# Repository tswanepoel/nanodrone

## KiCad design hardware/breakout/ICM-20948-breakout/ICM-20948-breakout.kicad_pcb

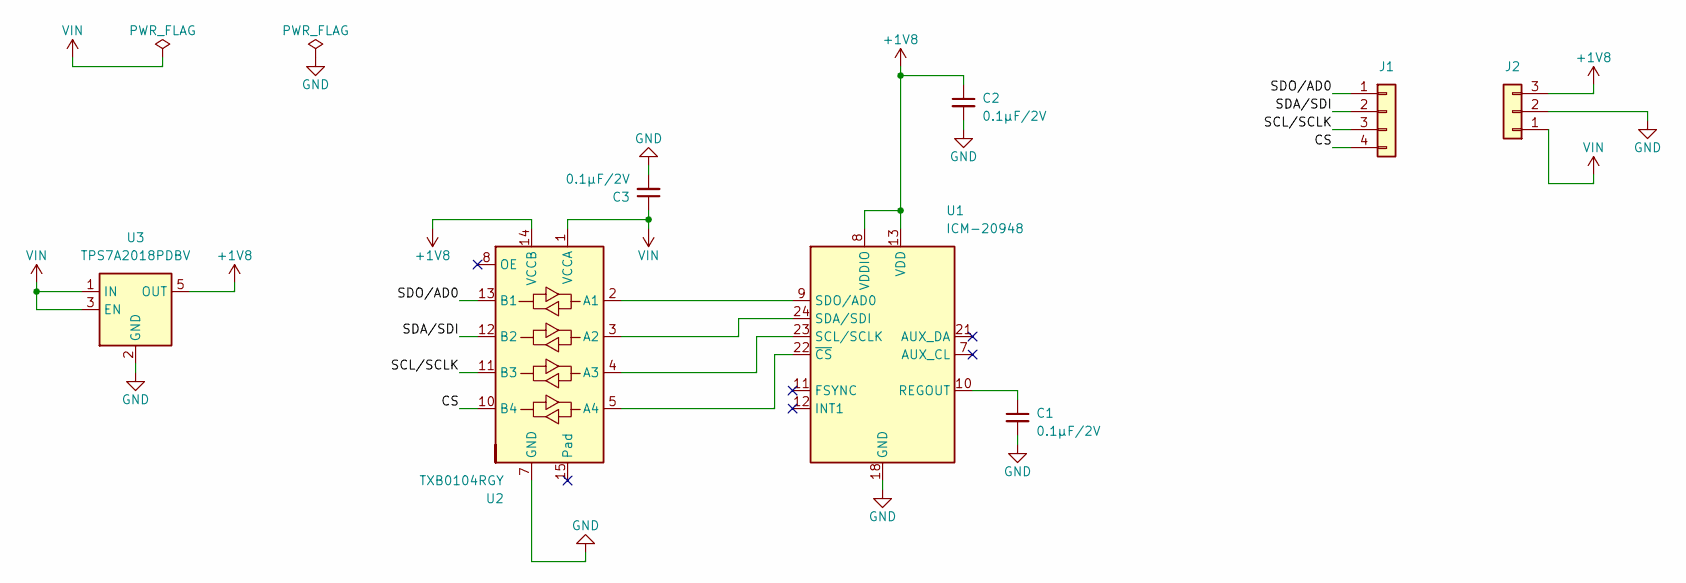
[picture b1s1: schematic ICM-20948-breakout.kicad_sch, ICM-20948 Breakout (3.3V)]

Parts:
C1, C2, C3: 0.1µF/2V; C_0603_1608Metric_Pad1.08x0.95mm_HandSolder
J1: Conn_01x04; PinHeader_1x04_P2.54mm_Vertical
J2: Conn_01x03; PinHeader_1x03_P2.54mm_Vertical
U1: ICM-20948; InvenSense_QFN-24_3x3mm_P0.4mm
U2: TXB0104RGY; Texas_S-PVQFN-N14
U3: TPS7A2018PDBV; SOT-23-5

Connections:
+1V8: C2.1, J2.3, U1.8 (VDDIO), U1.13 (VDD), U2.14 (VCCB), U3.5 (OUT)
/CS: J1.4, U2.10 (B4)
/SCL/SCLK: J1.3, U2.11 (B3)
/SDA/SDI: J1.2, U2.12 (B2)
/SDO/AD0: J1.1, U2.13 (B1)
GND: C1.2, C2.2, C3.2, J2.2, U1.18 (GND), U1.20 (GND), U2.7 (GND), U3.2 (GND)
unnamed: C1.1, U1.10 (REGOUT)
unnamed: U1.23 (SCL/SCLK), U2.4 (A3)
unnamed: U1.24 (SDA/SDI), U2.3 (A2)
unnamed: U1.9 (SDO/AD0), U2.2 (A1)
unnamed: U1.22 (~CS), U2.5 (A4)
VIN: C3.1, J2.1, U2.1 (VCCA), U3.1 (IN), U3.3 (EN)

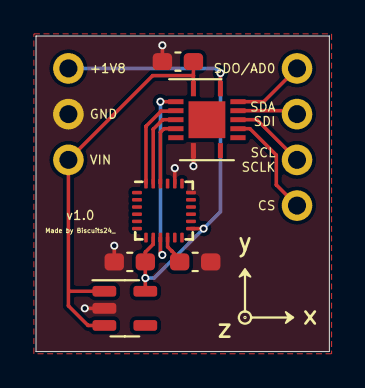
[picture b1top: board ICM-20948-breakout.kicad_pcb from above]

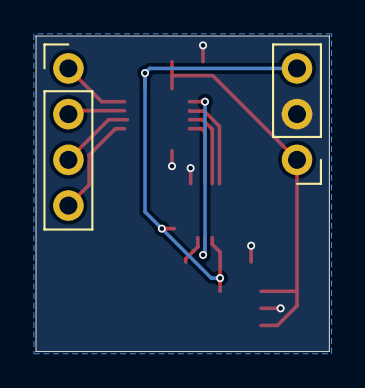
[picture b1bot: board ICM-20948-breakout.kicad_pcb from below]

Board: 2 copper layers, 16.3 x 17.5 mm, 8 parts (2 on the bottom side), 12 nets.

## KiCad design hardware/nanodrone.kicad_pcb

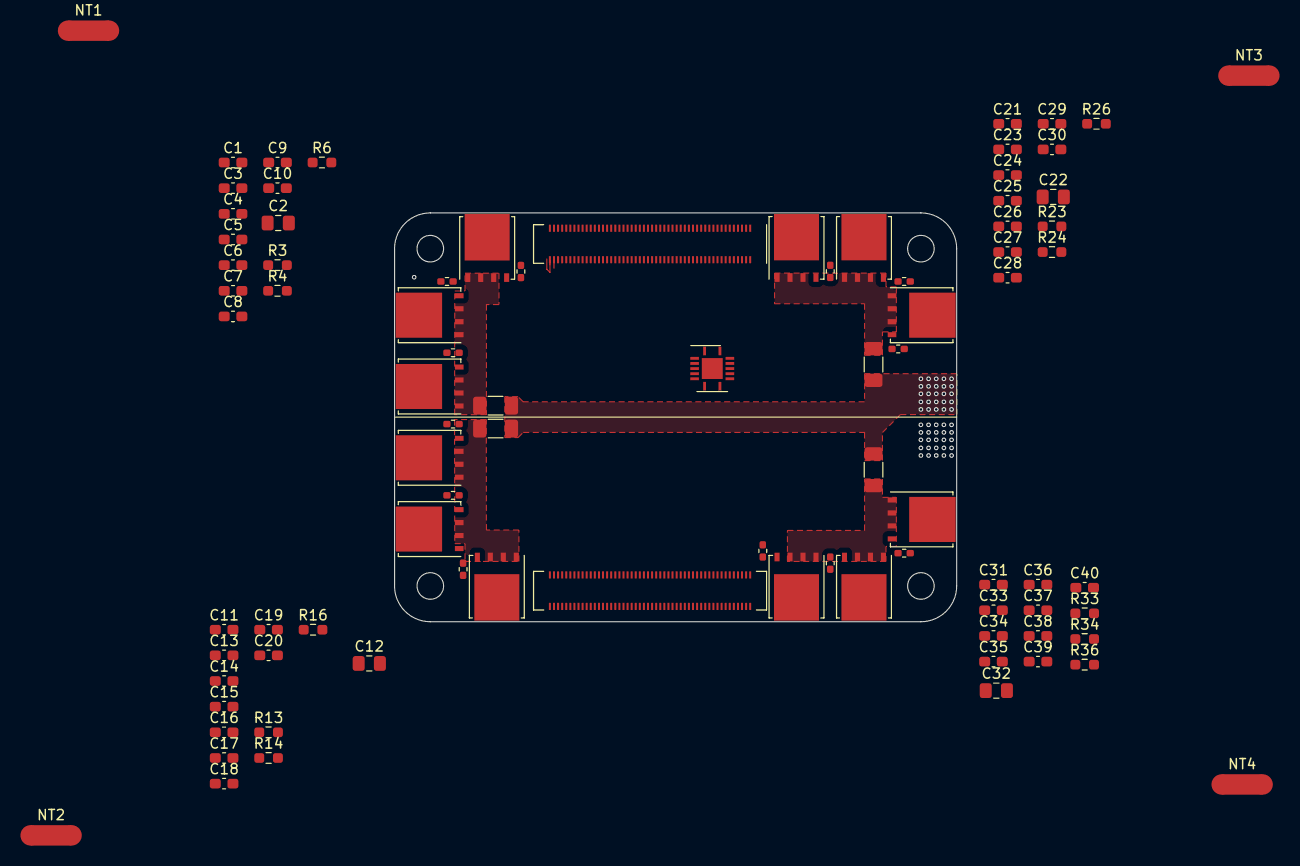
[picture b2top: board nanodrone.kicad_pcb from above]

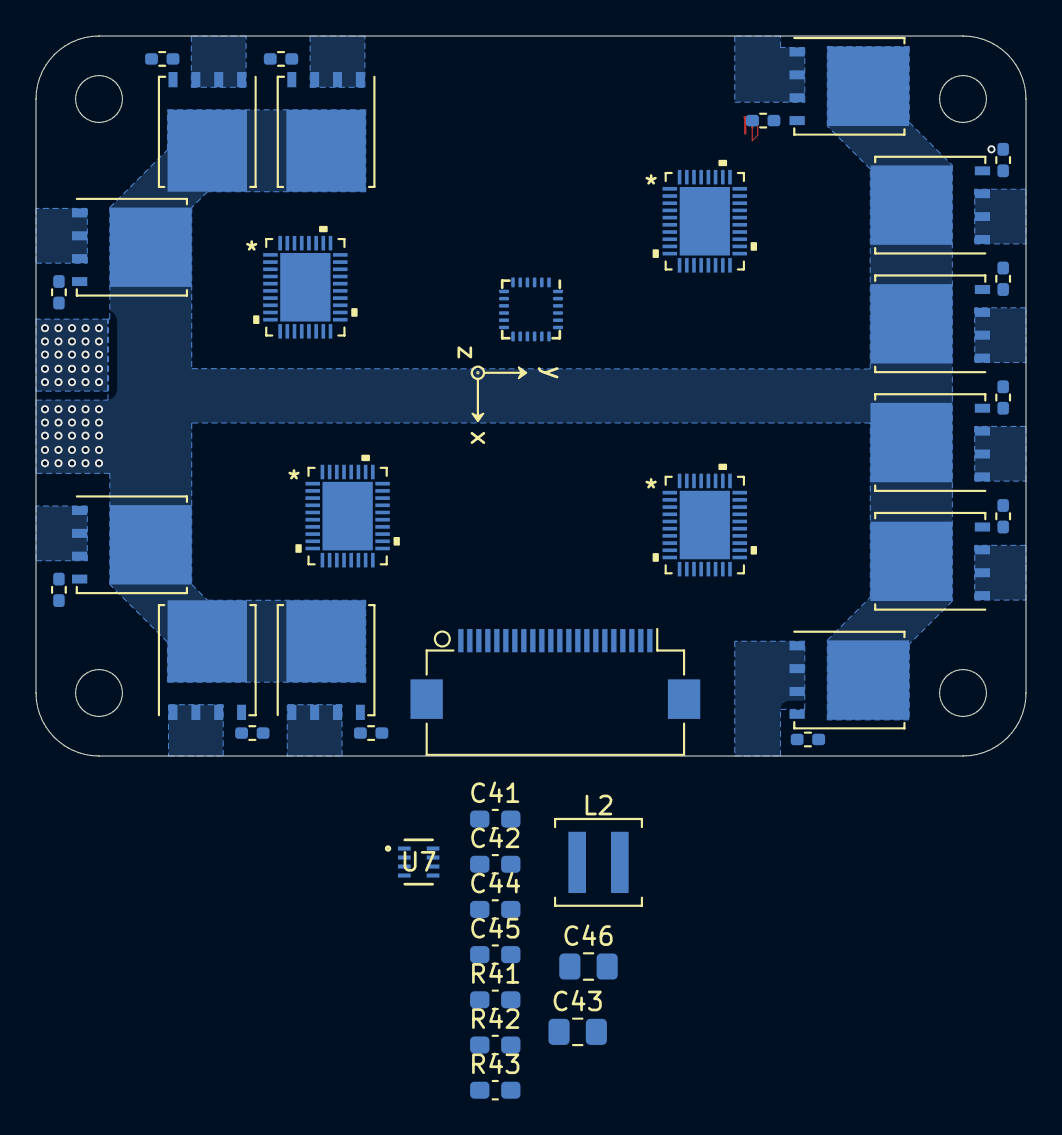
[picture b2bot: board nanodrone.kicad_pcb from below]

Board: 4 copper layers, 55.0 x 40.0 mm, 127 parts (41 on the bottom side), 126 nets.

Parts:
C1, C11, C21, C31: 0.1µF/25V; C_0603_1608Metric_Pad1.08x0.95mm_HandSolder
C2, C12, C22, C32: 10µF/25V; C_0805_2012Metric_Pad1.18x1.45mm_HandSolder
C3, C13, C23, C33: 470nF/25V; C_0603_1608Metric_Pad1.08x0.95mm_HandSolder
C4, C14, C24, C34: 10µF/25V; C_0603_1608Metric_Pad1.08x0.95mm_HandSolder
C5, C15, C25, C35: 1µF/10V; C_0603_1608Metric_Pad1.08x0.95mm_HandSolder
C6, C8, C9, C16, C18, C19, C26, C28, C29, C36, C38, C39: 1µF/25V; C_0603_1608Metric_Pad1.08x0.95mm_HandSolder
C7, C17, C27, C37: 1µF/4V; C_0603_1608Metric_Pad1.08x0.95mm_HandSolder
C10, C20, C30, C40: 1µF/6.3V; C_0603_1608Metric_Pad1.08x0.95mm_HandSolder
C41: 100nF/10V; C_0603_1608Metric_Pad1.08x0.95mm_HandSolder
C42: 100nF/25V; C_0603_1608Metric_Pad1.08x0.95mm_HandSolder
C43: 10µF/35V; C_0805_2012Metric_Pad1.18x1.45mm_HandSolder
C44: 33nF/10V; C_0603_1608Metric_Pad1.08x0.95mm_HandSolder
C45: 47pF/25V; C_0603_1608Metric_Pad1.08x0.95mm_HandSolder
C46: 47µF/10V; C_0805_2012Metric_Pad1.18x1.45mm_HandSolder
J1: Conn_01x22_Female; Hirose_FH12A-22S-0.5SH_1x22-1MP_P0.50mm_Horizontal
L2: 3.3µH; L_Coilcraft_XAL4030-XXX
Module1: ComputeModule4-CM4; Raspberry-Pi-4-Compute-Module
NT1, NT2, NT3, NT4: NetTie_2; NetTie-2_SMD_Pad2.0mm
Q1, Q2, Q3, Q4, Q5, Q6, Q7, Q8, Q9, Q10, Q11, Q12, Q13, Q14, Q15, Q16, Q17, Q18, Q19, Q20, Q21, Q22, Q23, Q24: BSC009NE2LS5; TDSON-8-1
R1, R2, R5, R7, R8, R9, R11, R12, R15, R17, R18, R19, R21, R22, R25, R27, R28, R29, R31, R32, R35, R37, R38, R39: 0Ω; R_0402_1005Metric_Pad0.72x0.64mm_HandSolder
R3, R4, R13, R14, R23, R24, R33, R34: 10kΩ; R_0603_1608Metric_Pad0.98x0.95mm_HandSolder
R6, R16, R26, R36: 5.1kΩ; R_0603_1608Metric_Pad0.98x0.95mm_HandSolder
R10, R20, R30, R40: 1mΩ/1W; R_1206_3216Metric_Pad1.30x1.75mm_HandSolder
R41: 19.6kΩ; C_0603_1608Metric_Pad1.08x0.95mm_HandSolder
R42: 52.3kΩ; C_0603_1608Metric_Pad1.08x0.95mm_HandSolder
R43: 10kΩ; C_0603_1608Metric_Pad1.08x0.95mm_HandSolder
U1, U2, U5, U6: MCT8329A; MCT8329A1IREER
U3: TXB0104RGY; Texas_S-PVQFN-N14
U4: ICM-20948; InvenSense_QFN-24_3x3mm_P0.4mm
U7: TPS62933FDRLR; SOT_33DRLR_TEX

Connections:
/CAM1_C_N: J1.8, Module1.127 (CAM1_C_N)
/CAM1_C_P: J1.9, Module1.129 (CAM1_C_P)
/CAM1_D0_N: J1.2, Module1.115 (CAM1_D0_N)
/CAM1_D0_P: J1.3, Module1.117 (CAM1_D0_P)
/CAM1_D1_N: J1.5, Module1.121 (CAM1_D1_N)
/CAM1_D1_P: J1.6, Module1.123 (CAM1_D1_P)
/CAM1_D2_N: J1.11, Module1.133 (CAM1_D2_N)
/CAM1_D2_P: J1.12, Module1.135 (CAM1_D2_P)
/CAM1_D3_N: J1.14, Module1.139 (CAM1_D3_N)
/CAM1_D3_P: J1.15, Module1.141 (CAM1_D3_P)
/SCL0: J1.20, Module1.80 (SCL0)
/SDA0: J1.21, Module1.82 (SDA0)
AGND: C30.2, C40.2, U5.25 (AGND), U6.25 (AGND)
AVDD: C5.1, C10.1, C15.1, C20.1, C25.1, C30.1, C35.1, C40.1, R6.1, R16.1, R26.1, R36.1, U1.2 (VREG), U1.26 (AVDD), U2.2 (VREG), U2.26 (AVDD), U5.2 (VREG), U5.26 (AVDD), U6.2 (VREG), U6.26 (AVDD)
DGND: U1.1 (DGND), U2.1 (DGND), U5.1 (DGND), U6.1 (DGND)
DVDD: C7.1, C17.1, C27.1, C37.1, U1.36 (DVDD), U2.36 (DVDD), U5.36 (DVDD), U6.36 (DVDD)
GND: C4.2, C10.2, C14.2, C20.2, C24.2, C34.2, J1.1, J1.4, J1.7, J1.10, J1.13, J1.16, J1.19, Module1.113 (GND), Module1.119 (GND), Module1.125 (GND), Module1.131 (GND), Module1.137 (GND), NT1.2, NT2.2, NT3.2, NT4.2, R3.2, R4.1, R13.2, R14.1, R23.2, R24.1, R33.2, R34.1, U1.25 (AGND), U2.25 (AGND)
unnamed: C45.1, C46.1, L2.2, R42.1
unnamed: Q1.4 (G), R1.1
unnamed: C6.2, Q1.1 (S), Q1.2 (S), Q1.3 (S), Q2.5 (D), U1.10 (SHA)
unnamed: Q2.4 (G), R2.1
unnamed: Q3.4 (G), R5.1
unnamed: C8.2, Q3.1 (S), Q3.2 (S), Q3.3 (S), Q4.5 (D), U1.14 (SHB)
unnamed: Q4.4 (G), R7.1
unnamed: Q5.4 (G), R8.1
unnamed: C9.2, Q5.1 (S), Q5.2 (S), Q5.3 (S), Q6.5 (D), U1.18 (SHC)
unnamed: Q6.4 (G), R9.1
unnamed: Q7.4 (G), R11.1
unnamed: C16.2, Q7.1 (S), Q7.2 (S), Q7.3 (S), Q8.5 (D), U2.10 (SHA)
unnamed: Q8.4 (G), R12.1
unnamed: Q9.4 (G), R15.1
unnamed: C18.2, Q9.1 (S), Q9.2 (S), Q9.3 (S), Q10.5 (D), U2.14 (SHB)
unnamed: Q10.4 (G), R17.1
unnamed: Q11.4 (G), R18.1
unnamed: C19.2, Q11.1 (S), Q11.2 (S), Q11.3 (S), Q12.5 (D), U2.18 (SHC)
unnamed: Q12.4 (G), R19.1
unnamed: Q13.4 (G), R21.1
unnamed: C26.2, Q13.1 (S), Q13.2 (S), Q13.3 (S), Q14.5 (D), U5.10 (SHA)
unnamed: Q14.4 (G), R22.1
unnamed: Q15.4 (G), R25.1
unnamed: C28.2, Q15.1 (S), Q15.2 (S), Q15.3 (S), Q16.5 (D), U5.14 (SHB)
unnamed: Q16.4 (G), R27.1
unnamed: Q17.4 (G), R28.1
unnamed: C29.2, Q17.1 (S), Q17.2 (S), Q17.3 (S), Q18.5 (D), U5.18 (SHC)
unnamed: Q18.4 (G), R29.1
unnamed: Q19.4 (G), R31.1
unnamed: C36.2, Q19.1 (S), Q19.2 (S), Q19.3 (S), Q20.5 (D), U6.10 (SHA)
unnamed: Q20.4 (G), R32.1
unnamed: Q21.4 (G), R35.1
unnamed: C38.2, Q21.1 (S), Q21.2 (S), Q21.3 (S), Q22.5 (D), U6.14 (SHB)
unnamed: Q22.4 (G), R37.1
unnamed: Q23.4 (G), R38.1
unnamed: C39.2, Q23.1 (S), Q23.2 (S), Q23.3 (S), Q24.5 (D), U6.18 (SHC)
unnamed: Q24.4 (G), R39.1
unnamed: R3.1, U1.34 (BRAKE)
unnamed: C6.1, U1.9 (BSTA)
unnamed: C8.1, U1.13 (BSTB)
unnamed: C9.1, U1.17 (BSTC)
unnamed: C3.2, U1.7 (CPH)
unnamed: C3.1, U1.6 (CPL)
unnamed: R4.2, U1.31 (DIR)
unnamed: R6.2, U1.28 (FG)
unnamed: R1.2, U1.11 (GHA)
unnamed: R5.2, U1.15 (GHB)
unnamed: R8.2, U1.19 (GHC)
unnamed: R2.2, U1.12 (GLA)
unnamed: R7.2, U1.16 (GLB)
unnamed: R9.2, U1.20 (GLC)
unnamed: C4.1, U1.8 (GVDD)
unnamed: Q2.1 (S), Q2.2 (S), Q2.3 (S), Q4.1 (S), Q4.2 (S), Q4.3 (S), Q6.1 (S), Q6.2 (S), Q6.3 (S), R10.2, U1.21 (LSS), U1.22 (SP)
unnamed: R13.1, U2.34 (BRAKE)
unnamed: C16.1, U2.9 (BSTA)
unnamed: C18.1, U2.13 (BSTB)
unnamed: C19.1, U2.17 (BSTC)
unnamed: C13.2, U2.7 (CPH)
unnamed: C13.1, U2.6 (CPL)
unnamed: R14.2, U2.31 (DIR)
unnamed: R16.2, U2.28 (FG)
unnamed: R11.2, U2.11 (GHA)
unnamed: R15.2, U2.15 (GHB)
unnamed: R18.2, U2.19 (GHC)
unnamed: R12.2, U2.12 (GLA)
unnamed: R17.2, U2.16 (GLB)
unnamed: R19.2, U2.20 (GLC)
unnamed: C14.1, U2.8 (GVDD)
unnamed: Q8.1 (S), Q8.2 (S), Q8.3 (S), Q10.1 (S), Q10.2 (S), Q10.3 (S), Q12.1 (S), Q12.2 (S), Q12.3 (S), R20.2, U2.21 (LSS), U2.22 (SP)
unnamed: U4.18 (GND), U4.20 (GND)
unnamed: R23.1, U5.34 (BRAKE)
unnamed: C26.1, U5.9 (BSTA)
unnamed: C28.1, U5.13 (BSTB)
unnamed: C29.1, U5.17 (BSTC)
unnamed: C23.2, U5.7 (CPH)
unnamed: C23.1, U5.6 (CPL)
unnamed: R24.2, U5.31 (DIR)
unnamed: R26.2, U5.28 (FG)
unnamed: R21.2, U5.11 (GHA)
unnamed: R25.2, U5.15 (GHB)
unnamed: R28.2, U5.19 (GHC)
unnamed: R22.2, U5.12 (GLA)
unnamed: R27.2, U5.16 (GLB)
unnamed: R29.2, U5.20 (GLC)
unnamed: C24.1, U5.8 (GVDD)
unnamed: Q14.1 (S), Q14.2 (S), Q14.3 (S), Q16.1 (S), Q16.2 (S), Q16.3 (S), Q18.1 (S), Q18.2 (S), Q18.3 (S), R30.2, U5.21 (LSS), U5.22 (SP)
unnamed: R33.1, U6.34 (BRAKE)
unnamed: C36.1, U6.9 (BSTA)
unnamed: C38.1, U6.13 (BSTB)
unnamed: C39.1, U6.17 (BSTC)
unnamed: C33.2, U6.7 (CPH)
unnamed: C33.1, U6.6 (CPL)
unnamed: R34.2, U6.31 (DIR)
unnamed: R36.2, U6.28 (FG)
unnamed: R31.2, U6.11 (GHA)
unnamed: R35.2, U6.15 (GHB)
unnamed: R38.2, U6.19 (GHC)
unnamed: R32.2, U6.12 (GLA)
unnamed: R37.2, U6.16 (GLB)
unnamed: R39.2, U6.20 (GLC)
unnamed: C34.1, U6.8 (GVDD)
unnamed: Q20.1 (S), Q20.2 (S), Q20.3 (S), Q22.1 (S), Q22.2 (S), Q22.3 (S), Q24.1 (S), Q24.2 (S), Q24.3 (S), R40.2, U6.21 (LSS), U6.22 (SP)
unnamed: C41.1, U7.6 (BST)
unnamed: C45.2, R42.2, R43.1, U7.8 (FB)
unnamed: R41.1, U7.1 (RT)
unnamed: C44.1, U7.7 (SS)
unnamed: C41.2, L2.1, U7.5 (SW)
PGND: C1.2, C2.2, C5.2, C7.2, C11.2, C12.2, C15.2, C17.2, C21.2, C22.2, C25.2, C27.2, C31.2, C32.2, C35.2, C37.2, C42.2, C43.2, C44.2, C46.2, NT1.1, NT2.1, NT3.1, NT4.1, R10.1, R20.1, R30.1, R40.1, R41.2, R43.2, U1.4 (PGND), U1.23 (SN), U2.4 (PGND), U2.23 (SN), U5.4 (PGND), U5.23 (SN), U6.4 (PGND), U6.23 (SN), U7.4 (GND)
PVDD: C1.1, C2.1, C11.1, C12.1, C21.1, C22.1, C31.1, C32.1, C42.1, C43.1, Q1.5 (D), Q3.5 (D), Q5.5 (D), Q7.5 (D), Q9.5 (D), Q11.5 (D), Q13.5 (D), Q15.5 (D), Q17.5 (D), Q19.5 (D), Q21.5 (D), Q23.5 (D), U1.5 (PVDD), U2.5 (PVDD), U5.5 (PVDD), U6.5 (PVDD), U7.3 (VIN)

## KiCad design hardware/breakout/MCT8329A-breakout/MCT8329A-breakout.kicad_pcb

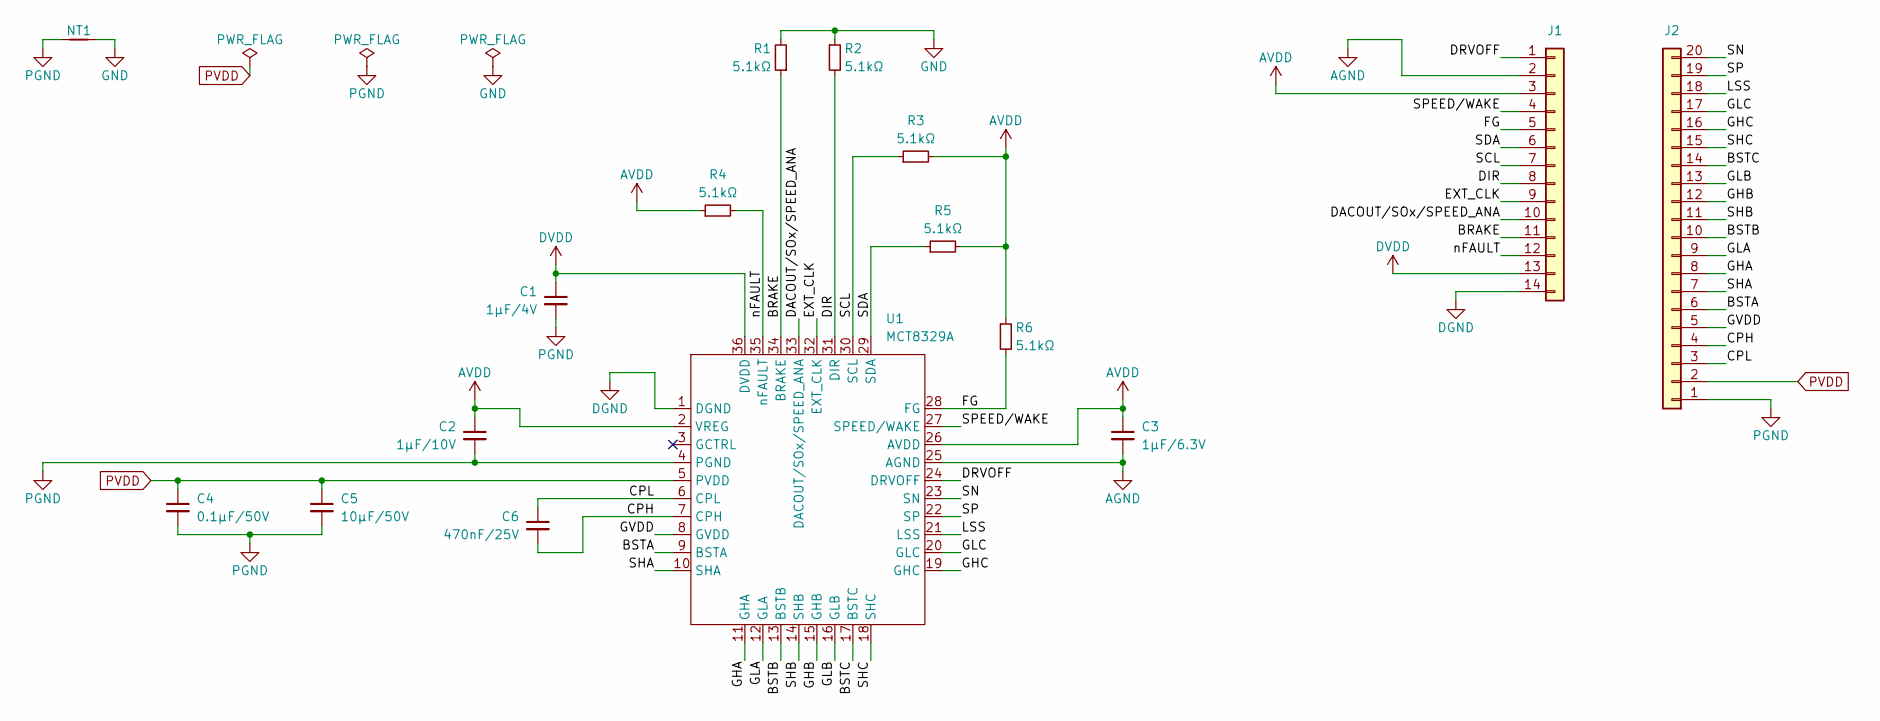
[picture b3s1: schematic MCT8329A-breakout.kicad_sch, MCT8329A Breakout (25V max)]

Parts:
C1: 1µF/4V; C_0603_1608Metric_Pad1.08x0.95mm_HandSolder
C2: 1µF/10V; C_0603_1608Metric_Pad1.08x0.95mm_HandSolder
C3: 1µF/6.3V; C_0603_1608Metric_Pad1.08x0.95mm_HandSolder
C4: 0.1µF/50V; C_0603_1608Metric_Pad1.08x0.95mm_HandSolder
C5: 10µF/50V; C_0805_2012Metric_Pad1.18x1.45mm_HandSolder
C6: 470nF/25V; C_0603_1608Metric_Pad1.08x0.95mm_HandSolder
J1: Conn_01x14; PinHeader_1x14_P2.54mm_Vertical
J2: Conn_01x20; PinHeader_1x20_P2.54mm_Vertical
NT1: NetTie_2; NetTie-2_SMD_Pad2.0mm
R1, R2, R3, R4, R5, R6: 5.1kΩ; R_0603_1608Metric_Pad0.98x0.95mm_HandSolder
U1: MCT8329A; MCT8329A1IREER

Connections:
/BRAKE: J1.11, R1.1, U1.34 (BRAKE)
/BSTA: J2.6, U1.9 (BSTA)
/BSTB: J2.10, U1.13 (BSTB)
/BSTC: J2.14, U1.17 (BSTC)
/CPH: C6.2, J2.4, U1.7 (CPH)
/CPL: C6.1, J2.3, U1.6 (CPL)
/DACOUT/SOx/SPEED_ANA: J1.10, U1.33 (DACOUT/SOx/SPEED_ANA)
/DIR: J1.8, R2.2, U1.31 (DIR)
/DRVOFF: J1.1, U1.24 (DRVOFF)
/EXT_CLK: J1.9, U1.32 (EXT_CLK)
/FG: J1.5, R6.2, U1.28 (FG)
/GHA: J2.8, U1.11 (GHA)
/GHB: J2.12, U1.15 (GHB)
/GHC: J2.16, U1.19 (GHC)
/GLA: J2.9, U1.12 (GLA)
/GLB: J2.13, U1.16 (GLB)
/GLC: J2.17, U1.20 (GLC)
/GVDD: J2.5, U1.8 (GVDD)
/LSS: J2.18, U1.21 (LSS)
/SCL: J1.7, R3.1, U1.30 (SCL)
/SDA: J1.6, R5.1, U1.29 (SDA)
/SHA: J2.7, U1.10 (SHA)
/SHB: J2.11, U1.14 (SHB)
/SHC: J2.15, U1.18 (SHC)
/SN: J2.20, U1.23 (SN)
/SP: J2.19, U1.22 (SP)
/SPEED/WAKE: J1.4, U1.27 (SPEED/WAKE)
/nFAULT: J1.12, R4.2, U1.35 (nFAULT)
AGND: C3.2, J1.2, U1.25 (AGND)
AVDD: C2.1, C3.1, J1.3, R3.2, R4.1, R5.2, R6.1, U1.2 (VREG), U1.26 (AVDD)
DGND: J1.14, U1.1 (DGND)
DVDD: C1.1, J1.13, U1.36 (DVDD)
GND: NT1.2, R1.2, R2.1, U1.37; also elsewhere on the board
PGND: C1.2, C2.2, C4.2, C5.2, J2.1, NT1.1, U1.4 (PGND); also elsewhere on the board
PVDD: C4.1, C5.1, J2.2, U1.5 (PVDD)

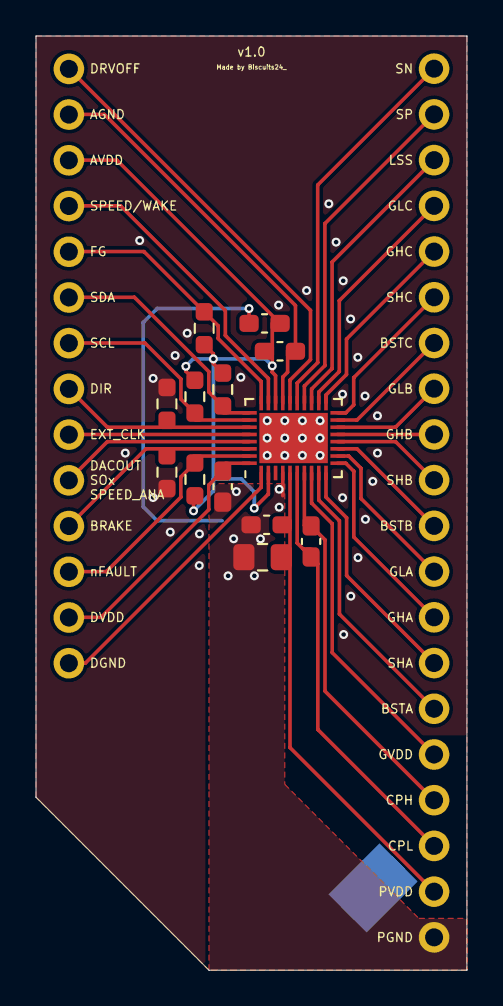
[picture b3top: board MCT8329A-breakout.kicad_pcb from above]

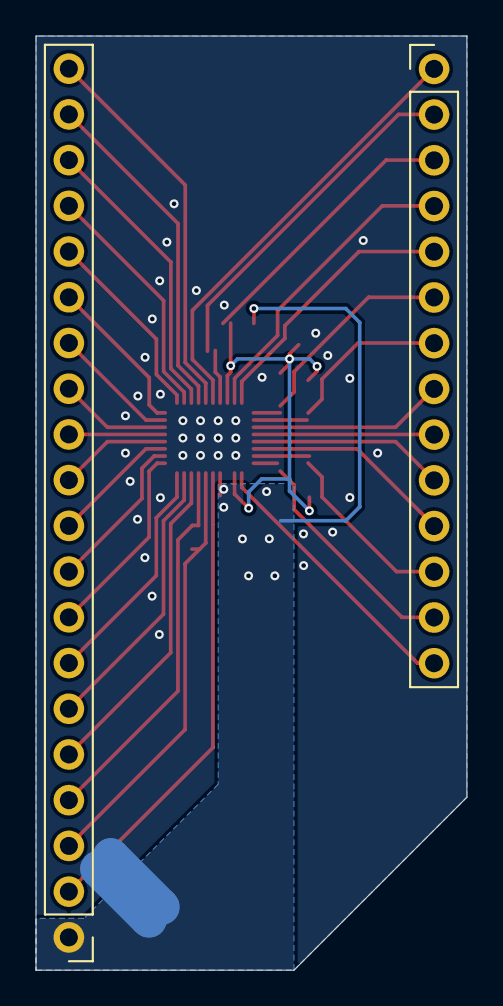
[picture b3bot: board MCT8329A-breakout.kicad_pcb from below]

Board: 2 copper layers, 23.9 x 51.9 mm, 17 parts (4 on the bottom side), 35 nets.

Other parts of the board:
NT1#2: NetTie_2; NetTie-2_SMD_Pad2.0mm

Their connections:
GND: NT1#2.2; also elsewhere on the board
PGND: NT1#2.1; also elsewhere on the board

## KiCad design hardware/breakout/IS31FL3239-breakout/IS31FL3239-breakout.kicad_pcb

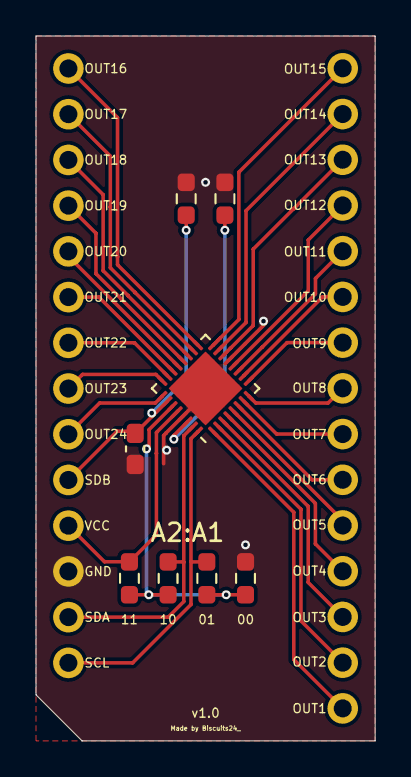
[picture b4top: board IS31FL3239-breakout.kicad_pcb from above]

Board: 2 copper layers, 18.8 x 39.2 mm, 8 parts (0 on the bottom side), 7 nets.

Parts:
C1: 0.1μF/5V; C_0603_1608Metric_Pad1.08x0.95mm_HandSolder
R1: 100kΩ; R_0603_1608Metric_Pad0.98x0.95mm_HandSolder
R2: 3.3kΩ; R_0603_1608Metric_Pad0.98x0.95mm_HandSolder
R3, R4, R5, R6: R_0603_1608Metric_Pad0.98x0.95mm_HandSolder
U1: QFN-32-1EP_4x4mm_P0.4mm_EP2.9x2.9mm

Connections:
AD: R3.1, R4.1, R5.1, R6.1, U1.27
GND: C1.2, R1.2, R2.2, R6.2, U1.13, U1.29, U1.33
ISET: R2.1, U1.30
SCL: R5.2, U1.32
SDA: R4.2, U1.31
SDB: C1.1, R1.1, U1.26
VCC: R3.2, U1.28

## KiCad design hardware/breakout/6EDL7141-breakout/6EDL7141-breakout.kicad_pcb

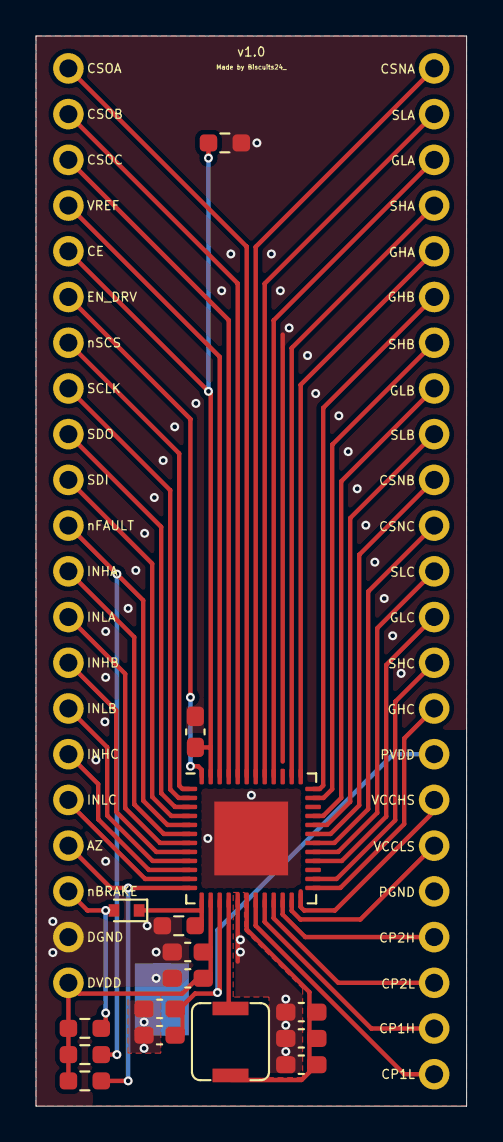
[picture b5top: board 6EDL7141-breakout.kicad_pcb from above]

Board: 2 copper layers, 23.9 x 59.5 mm, 16 parts (0 on the bottom side), 11 nets.

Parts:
C1, C4: 0.1μF/25V; C_0603_1608Metric_Pad1.08x0.95mm_HandSolder
C2: 0.1μF/10V; C_0603_1608Metric_Pad1.08x0.95mm_HandSolder
C3: 10μF/10V; C_0603_1608Metric_Pad1.08x0.95mm_HandSolder
C5: 4.7μF/25V; C_0603_1608Metric_Pad1.08x0.95mm_HandSolder
C6: 0.1μF/16V; C_0603_1608Metric_Pad1.08x0.95mm_HandSolder
C7, C8: 22μF/16V; C_0603_1608Metric_Pad1.08x0.95mm_HandSolder
D1: 30V/500mA; D_SOD-523
L1: L_Bourns_SRP4020TA
R1: 100kΩ; R_0603_1608Metric_Pad0.98x0.95mm_HandSolder
R2: 3.3kΩ; R_0603_1608Metric_Pad0.98x0.95mm_HandSolder
R3, R4, R5: 10kΩ; R_0603_1608Metric_Pad0.98x0.95mm_HandSolder
U1: VQFN-48-1EP_7x7mm_P0.5mm_EP4.1x4.1mm

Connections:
AZ: R5.1, U1.12
CE: C1.1, R1.1, U1.47
DGND: C1.2, C2.2, C3.2, R1.2, R2.2, U1.49
DVDD: C2.1, C3.1, R3.2, R4.2, R5.2, U1.14
PGND: C4.2, C5.2, C6.2, C7.2, C8.2, U1.17
PH: L1.1, U1.16
PVDD: C4.1, C5.1, U1.15
VDDB: C6.1, C7.1, C8.1, L1.2, U1.18
VSENSE/nBRAKE: D1.1, R2.1, U1.13
nBRAKE: D1.2, R3.1
nFAULT: R4.1, U1.5

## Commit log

2023-04-09 Add breakout for MCT8329A.
2023-04-10 Add PCB for MCT8328A breakout.
2023-04-11 Finish ooard setup and add pin labels.
2023-04-12 Add breakout boards for 6EDL7141 and IS31FL3239, and SVGs.
2023-04-17 Add ICM-20948 breakout.
2023-05-05 Tidy up component references. Add project for MCT8329A driver.
2023-05-05 Move fabrication files for MCT8329A.
2023-05-05 Add enum extensions for descriptions.
2023-05-05 Add descriptions for hardware config.
2023-05-06 Add descriptions for gate driver config.
2023-05-06 Add descriptions for device state.
2023-05-06 Link missing code files. Add more descriptions.
2023-05-06 Add more descriptions.
2023-05-06 Add enums for fault config.
2023-05-10 Add more configuration for MCT8329A.
2023-05-12 Add more descriptions for MCT8329A.

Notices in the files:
parts and their libraries:
Copyright 2021 Accelerated Designs. All rights reserved.
